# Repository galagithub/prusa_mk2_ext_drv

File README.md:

This is a PCB made to replace the X and Y drivers used the Prusa MK2(S) or MK2.5(S) series of 3D printers.

A closed source kit can be purchased on the web, but the cost is prohibitive for large quantities.
So I have scoured the web for info about the controller used in the 3D printer, MiniRambo v1.3.
Eventually, I managed to compile the schematics enclosed in this github project.

I have used KiCAD v5.1 to design a PCB similar in dimensions to the closed source kit.
Reason being the availability of ready made 3D enclosure(s), the recommended one can be found here:
https://www.thingiverse.com/thing:2777899

Dimensions for the PCB were "recovered" using MeshLab on the above 3D enclosure(s).

Resources:
1) https://reprap.org/wiki/MiniRambo
2) https://reprap.org/wiki/RAMPS_1.4
3) https://reprap.org/wiki/StepStick
4) https://learn.watterott.com/silentstepstick/pinconfig/tmc2209/
5) https://www.thingiverse.com/thing:2777899
6) https://vmod.wordpress.com/prusa-mk2s-ext-driver-board-v2-3/
7) https://www.kicad.org/

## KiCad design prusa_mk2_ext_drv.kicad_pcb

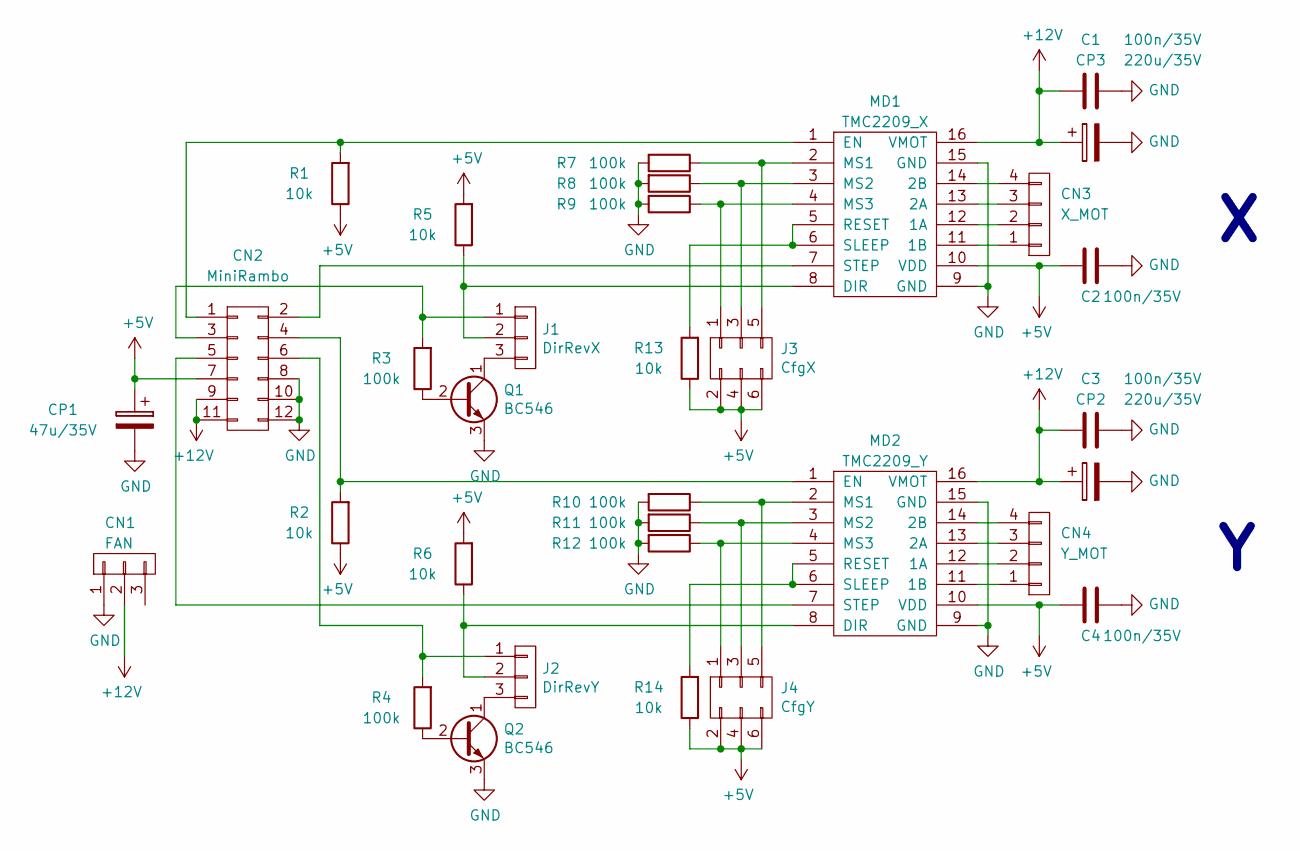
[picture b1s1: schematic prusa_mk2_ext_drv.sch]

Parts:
C1, C2, C3, C4: 100n/35V; C_Rect_L7_W2.5_P5
CN1: FAN; Fan_Pin_Header_Straight_1x03
CN2: MiniRambo; IDC_Header_Straight_12pins
CN3: X_MOT; Molex_70553_4P
CN4: Y_MOT; Molex_70553_4P
CP1: 47u/35V; CP_Radial_D6.3mm_P2.50mm
CP2, CP3: 220u/35V; CP_Radial_D8.0mm_P3.50mm
J1: DirRevX; JP_2.54mm_3PIN
J2: DirRevY; JP_2.54mm_3PIN
J3: CfgX; JP_2.54mm_2x3PIN
J4: CfgY; JP_2.54mm_2x3PIN
MD1: TMC2209_X; STEPSTICK
MD2: TMC2209_Y; STEPSTICK
Q1, Q2: BC546; TO-92_Inline_Wide
R1, R2, R5, R6, R13, R14: 10k; R_Axial_DIN0204_L3.6mm_D1.6mm_P5.08mm_Horizontal
R3, R4, R7, R8, R9, R10, R11, R12: 100k; R_Axial_DIN0204_L3.6mm_D1.6mm_P5.08mm_Horizontal

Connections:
+5V: C2.2, C4.2, CN2.7, CP1.1, J3.2, J3.4, J3.6, J4.2, J4.4, J4.6, MD1.10 (VDD), MD2.10 (VDD), R1.1, R2.1, R5.2, R6.2, R13.1, R14.1
+12V: C1.2, C3.2, CN1.2, CN2.9, CN2.11, CP2.1, CP3.1, MD1.16 (VMOT), MD2.16 (VMOT)
GND: C1.1, C2.1, C3.1, C4.1, CN1.1, CN2.8, CN2.10, CN2.12, CP1.2, CP2.2, CP3.2, MD1.9 (GND), MD1.15 (GND), MD2.9 (GND), MD2.15 (GND), Q1.3 (E), Q2.3 (E), R7.2, R8.2, R9.2, R10.2, R11.2, R12.2
unnamed: CN2.1, MD1.1 (EN), R1.2
unnamed: CN2.2, MD1.7 (STEP)
unnamed: CN2.3, J1.1, R3.2
unnamed: CN2.4, MD2.1 (EN), R2.2
unnamed: CN2.5, MD2.7 (STEP)
unnamed: CN2.6, J2.1, R4.2
unnamed: CN3.1, MD1.11 (1B)
unnamed: CN3.2, MD1.12 (1A)
unnamed: CN3.3, MD1.13 (2A)
unnamed: CN3.4, MD1.14 (2B)
unnamed: CN4.1, MD2.11 (1B)
unnamed: CN4.2, MD2.12 (1A)
unnamed: CN4.3, MD2.13 (2A)
unnamed: CN4.4, MD2.14 (2B)
unnamed: J1.2, MD1.8 (DIR), R5.1
unnamed: J1.3, Q1.1 (C)
unnamed: J2.2, MD2.8 (DIR), R6.1
unnamed: J2.3, Q2.1 (C)
unnamed: J3.1, MD1.4 (MS3), R9.1
unnamed: J3.3, MD1.3 (MS2), R8.1
unnamed: J3.5, MD1.2 (MS1), R7.1
unnamed: J4.1, MD2.4 (MS3), R12.1
unnamed: J4.3, MD2.3 (MS2), R11.1
unnamed: J4.5, MD2.2 (MS1), R10.1
unnamed: MD1.5 (RESET), MD1.6 (SLEEP), R13.2
unnamed: MD2.5 (RESET), MD2.6 (SLEEP), R14.2
unnamed: Q1.2 (B), R3.1
unnamed: Q2.2 (B), R4.1

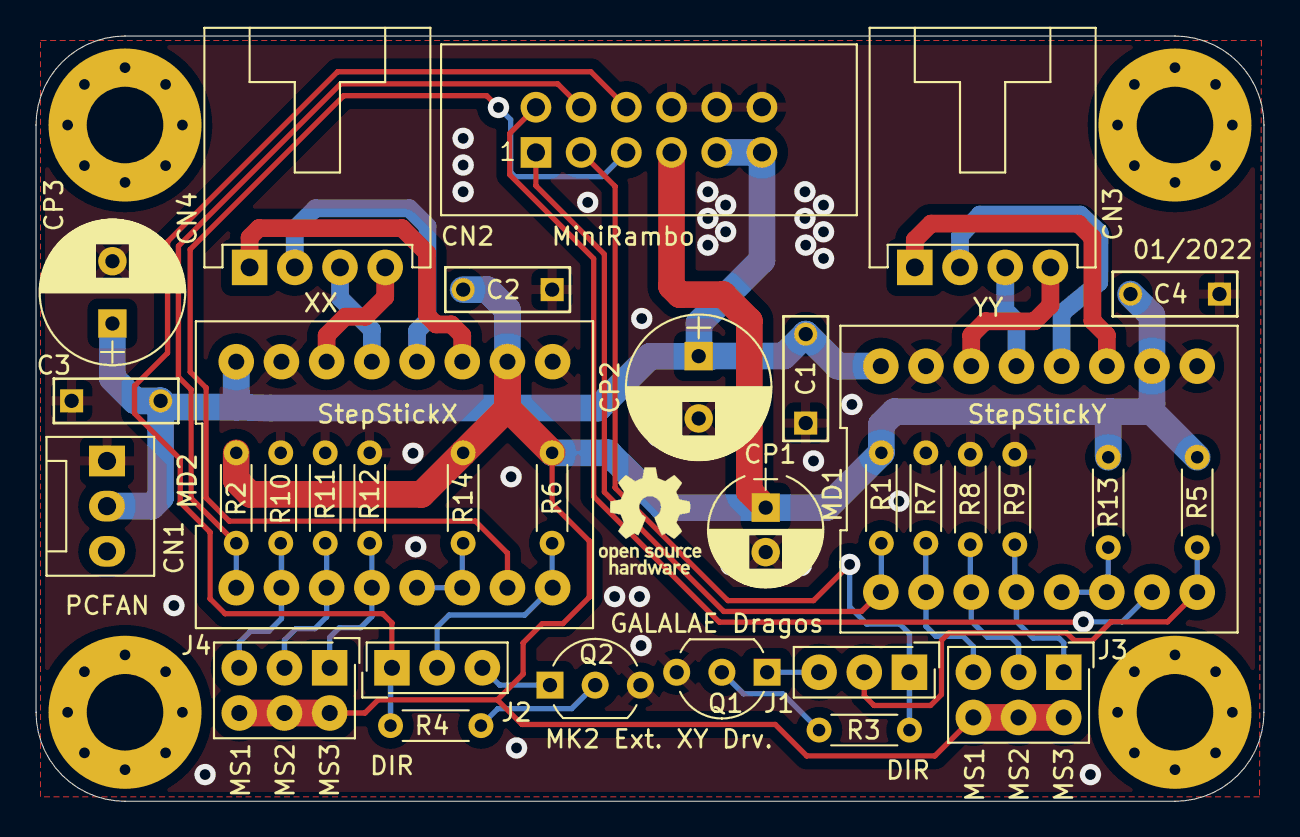
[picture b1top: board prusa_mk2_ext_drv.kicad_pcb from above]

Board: 2 copper layers, 69.0 x 43.0 mm, 33 parts (0 on the bottom side), 31 nets.

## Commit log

2022-01-15 Initial PCB ready for release
2022-01-15 Add render and fix shorting via.
2022-01-17 Initial version was sent to manufacturing, also made cosmetic changes and DRC with the new KiCAD v.6.0
2022-01-19 Upload PCB backup files
